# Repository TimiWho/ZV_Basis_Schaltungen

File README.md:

# ZV_Basis_Schaltungen

<!-- BEGIN LATEST DOWNLOAD BUTTON -->

<!-- END LATEST DOWNLOAD BUTTON -->

## V0.1 / 250228
- [ ] Basis Schaltungen wie ich sie auf meinen Platinen verwende

# Lizenz und Haftungsausschluss

Dieses Hardware-Design wird unter der CERN Open Hardware Licence Version 2 (CERN-OHL-P-2.0) veröffentlicht. Das bedeutet:

Jeder darf dieses Design frei nutzen, ändern und weitergeben.
Änderungen müssen ebenfalls unter der CERN-OHL veröffentlicht werden.
Eine Kopie der Lizenz muss beigefügt werden.
Die vollständigen Lizenzbedingungen sind hier zu finden:
CERN-OHL-P-2.0

Haftungsausschluss:
Dieses Design wird ohne jegliche Gewährleistung bereitgestellt. Es wird ohne Mängelgewähr veröffentlicht, ohne Garantie auf Funktionalität, Sicherheit oder Eignung für einen bestimmten Zweck. Die Nutzung erfolgt auf eigene Gefahr. Der Autor übernimmt keine Haftung für Schäden, die durch die Nutzung entstehen.

Durch die Verwendung dieses Designs erklärst du dich mit diesen Bedingungen einverstanden.

[TimiWho](https://timi.at/)

```
TTL AC 220V Isolation Modul SCM Test Board
```

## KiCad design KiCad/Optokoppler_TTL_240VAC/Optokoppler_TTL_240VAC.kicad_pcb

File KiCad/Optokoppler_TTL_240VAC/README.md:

# Optokoppler_TTL_240VAC

<!-- BEGIN LATEST DOWNLOAD BUTTON -->

<!-- END LATEST DOWNLOAD BUTTON -->

## V0.1 / 250317
- [ ] Doku folgt

# Lizenz und Haftungsausschluss

Dieses Hardware-Design wird unter der CERN Open Hardware Licence Version 2 (CERN-OHL-P-2.0) veröffentlicht. Das bedeutet:

Jeder darf dieses Design frei nutzen, ändern und weitergeben.
Änderungen müssen ebenfalls unter der CERN-OHL veröffentlicht werden.
Eine Kopie der Lizenz muss beigefügt werden.
Die vollständigen Lizenzbedingungen sind hier zu finden:
CERN-OHL-P-2.0

Haftungsausschluss:
Dieses Design wird ohne jegliche Gewährleistung bereitgestellt. Es wird ohne Mängelgewähr veröffentlicht, ohne Garantie auf Funktionalität, Sicherheit oder Eignung für einen bestimmten Zweck. Die Nutzung erfolgt auf eigene Gefahr. Der Autor übernimmt keine Haftung für Schäden, die durch die Nutzung entstehen.

Durch die Verwendung dieses Designs erklärst du dich mit diesen Bedingungen einverstanden.

[TimiWho](https://timi.at/)

```

```

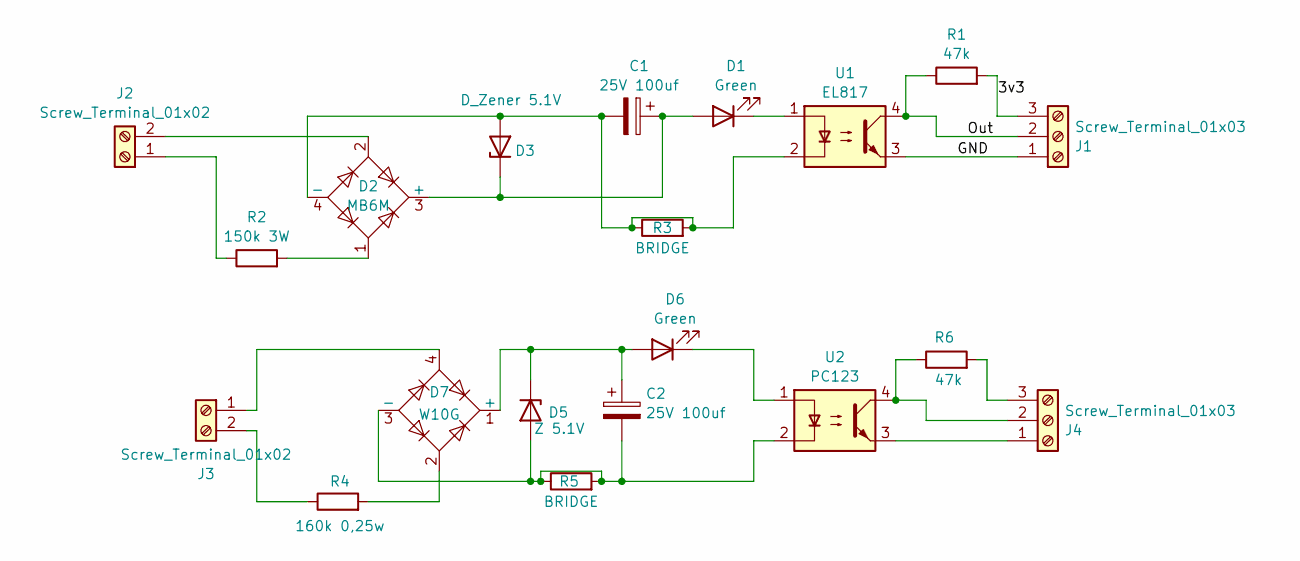
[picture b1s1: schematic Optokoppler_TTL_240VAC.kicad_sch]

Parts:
C1, C2: 25V 100uf; CP_Radial_D6.3mm_P2.50mm
D1, D6: Green; LED_D5.0mm_Clear
D2: MB6M; Diode_Bridge_DIP-4_W5.08mm_P2.54mm
D3: D_Zener 5.1V; D_DO-35_SOD27_P2.54mm_Vertical_AnodeUp
D5: Z 5.1V; D_DO-35_SOD27_P10.16mm_Horizontal
D7: W10G; Diode_Bridge_Round_D9.8mm
J1, J4: Screw_Terminal_01x03; TerminalBlock_Phoenix_1x03_P5.08mm_Horizontal
J2, J3: Screw_Terminal_01x02; TerminalBlock_Phoenix_1x02_P5.08mm_Horizontal
R1, R6: 47k; R_Vertical_P2.54mm
R2: 150k 3W; R_Horizontal_P10.16mm
R3, R5: BRIDGE; R_Horizontal_P10.16mm
R4: 160k 0,25w; R_Horizontal_P12.7mm
U1: EL817; DIP-4_W7.62mm
U2: PC123; DIP-4_W7.62mm

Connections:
/3v3: J1.3, R1.2
/GND: J1.1, U1.3
/Out: J1.2, R1.1, U1.4
unnamed: C1.1, D1.2 (A), D2.3 (+), D3.1 (K)
unnamed: D1.1 (K), U1.1
unnamed: C1.2, D2.4 (-), D3.2 (A), R3.1, R3.2, U1.2
unnamed: D2.1, R2.2
unnamed: C2.2, D5.2 (A), D7.3 (-), R5.1, R5.2, U2.2
unnamed: C2.1, D5.1 (K), D6.2 (A), D7.1 (+)
unnamed: D6.1 (K), U2.1
unnamed: D7.2, R4.2
unnamed: J2.1, R2.1
unnamed: D2.2, J2.2
unnamed: D7.4, J3.1
unnamed: J3.2, R4.1
unnamed: J4.1, U2.3
unnamed: J4.2, R6.1, U2.4
unnamed: J4.3, R6.2

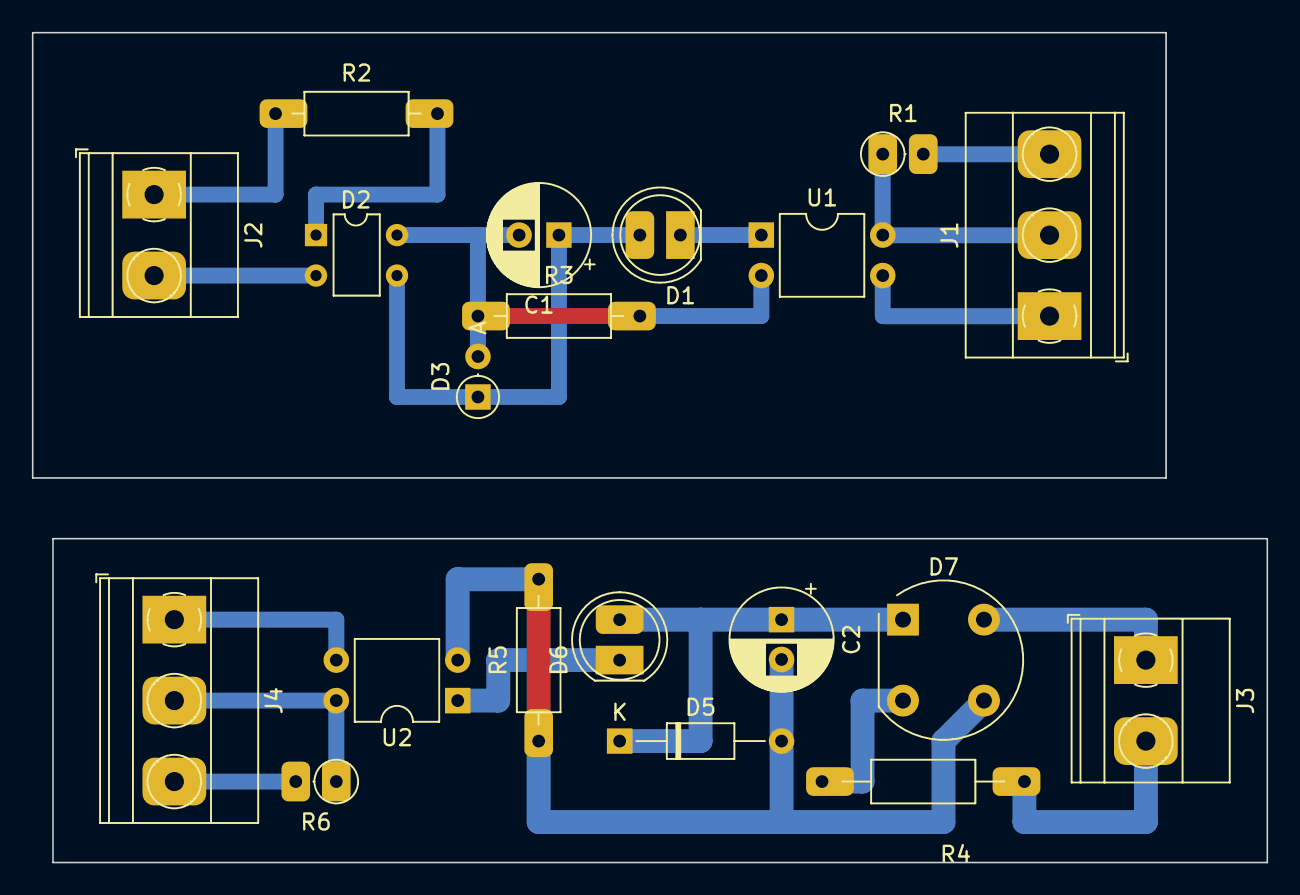
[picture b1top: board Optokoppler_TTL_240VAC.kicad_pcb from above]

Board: 2 copper layers, 77.5 x 52.1 mm, 20 parts (0 on the bottom side), 18 nets.

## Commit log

2025-03-30 datasheed
